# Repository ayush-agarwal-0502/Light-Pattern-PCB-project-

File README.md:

# Light-Pattern-PCB-Project-

Fascinating patterns of glowing LED lights made by me on proteus and eagle cad . ( Also called Diwali / Christmas lights)

Skills - Digital Electronics , PCB desgining 

Softwares involved - Proteus , Eagle CAD 

Digital electronics concepts involved - Jhonson counter with removed feedback , clock frequency divider , demux, astable multivibrator, monostable multivibrator using 555 timer 

Please see the video demostration of the lighting system , the file is uploaded in this repository .

Also see ADDITIONAL ideas file for other circuits for light patterns which I invented but haven't implemented yet .

# Proteus image 

# Eagle CAD schematic 

# Eagle CAD Board file 

# Gerber File View

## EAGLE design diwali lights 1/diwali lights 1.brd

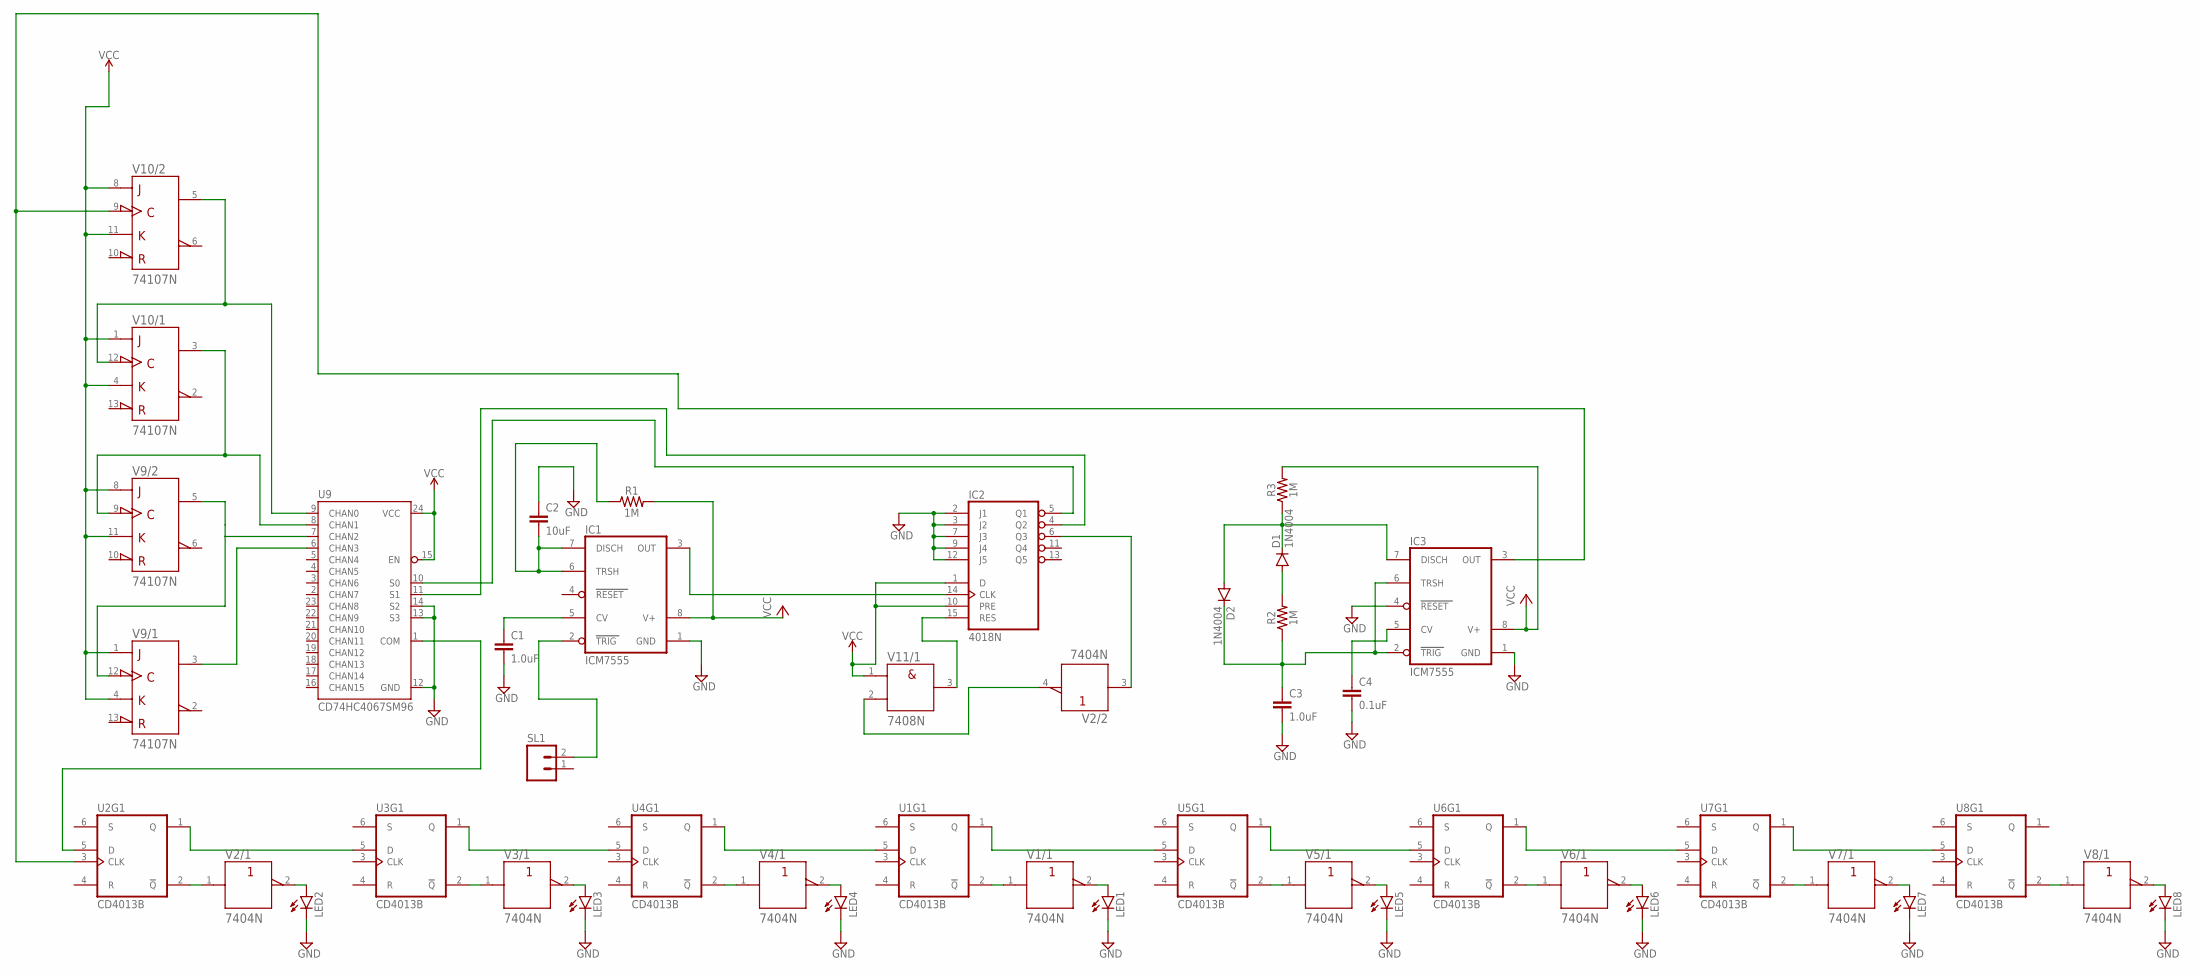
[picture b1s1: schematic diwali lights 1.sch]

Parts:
C1, C3: 1.0uF; 0402
C2: 10uF; 0805
C4: 0.1uF; 0402
D1, D2: 1N4004; DO41-10
IC1, IC3: ICM7555; DIL08
IC2: 4018N; DIL16
LED1, LED2, LED3, LED4, LED5, LED6, LED7, LED8: LED5MM
R1: 1M; 0402
R2, R3: 1M; AXIAL-0.3
SL1: M02; 02P
U1, U2, U3, U4, U5, U6, U7, U8: CD4013B; DIP14-KIT
U9: CD74HC4067SM96; SSOP24
V1, V2, V3, V4, V5, V6, V7, V8: 7404N; DIL14
V9, V10: 74107N; DIL14
V11: 7408N; DIL14

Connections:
+UB: V1.14 (+UB), V2.14 (+UB), V3.14 (+UB), V4.14 (+UB), V5.14 (+UB), V6.14 (+UB), V7.14 (+UB), V8.14 (+UB), V9.14 (+UB), V10.14 (+UB), V11.14 (+UB)
-UB: V1.7 (-UB), V2.7 (-UB), V3.7 (-UB), V4.7 (-UB), V5.7 (-UB), V6.7 (-UB), V7.7 (-UB), V8.7 (-UB), V9.7 (-UB), V10.7 (-UB), V11.7 (-UB)
GND: C1.2, C2.1, C3.2, C4.2, IC1.1 (GND), IC2.2 (J1), IC2.3 (J2), IC2.7 (J3), IC2.9 (J4), IC2.12 (J5), IC3.1 (GND), IC3.4 (RESET), LED1.K (C), LED2.K (C), LED3.K (C), LED4.K (C), LED5.K (C), LED6.K (C), LED7.K (C), LED8.K (C), U9.12 (GND), U9.13 (S3), U9.14 (S2)
unnamed: U1.2 (!Q), V1.1 (A)
unnamed: LED1.A, V1.2 (Y)
unnamed: U2.2 (!Q), V2.1 (A)
unnamed: LED2.A, V2.2 (Y)
unnamed: U3.2 (!Q), V3.1 (A)
unnamed: LED3.A, V3.2 (Y)
unnamed: U4.2 (!Q), V4.1 (A)
unnamed: LED4.A, V4.2 (Y)
unnamed: U5.2 (!Q), V5.1 (A)
unnamed: LED5.A, V5.2 (Y)
unnamed: U6.2 (!Q), V6.1 (A)
unnamed: LED6.A, V6.2 (Y)
unnamed: U7.2 (!Q), V7.1 (A)
unnamed: LED7.A, V7.2 (Y)
unnamed: U8.2 (!Q), V8.1 (A)
unnamed: LED8.A, V8.2 (Y)
unnamed: U2.1 (Q), U3.5 (D)
unnamed: U7.1 (Q), U8.5 (D)
unnamed: U3.1 (Q), U4.5 (D)
unnamed: U1.5 (D), U4.1 (Q)
unnamed: U1.1 (Q), U5.5 (D)
unnamed: U5.1 (Q), U6.5 (D)
unnamed: U6.1 (Q), U7.5 (D)
unnamed: U9.6 (CHAN3), V9.3 (Q)
unnamed: U2.5 (D), U9.1 (COM)
unnamed: U9.9 (CHAN0), V10.5 (Q), V10.12 (CLK)
unnamed: U9.8 (CHAN1), V9.9 (CLK), V10.3 (Q)
unnamed: U9.7 (CHAN2), V9.5 (Q), V9.12 (CLK)
unnamed: C3.1, D2.C, IC3.2 (TRIG), IC3.6 (TRSH), R2.P$1 (1)
unnamed: C2.2, IC1.6 (TRSH), IC1.7 (DISCH), R1.1
unnamed: C1.1, IC1.5 (CV)
unnamed: IC1.2 (TRIG), SL1.2
unnamed: IC2.6 (Q3), V2.3 (A)
unnamed: V2.4 (Y), V11.2 (B)
unnamed: IC1.3 (OUT), IC2.14 (CLK)
unnamed: IC2.15 (RES), V11.3 (Y)
unnamed: IC2.5 (Q1), U9.10 (S0)
unnamed: IC2.4 (Q2), U9.11 (S1)
unnamed: D1.A, R2.P$2 (2)
unnamed: D1.C, D2.A, IC3.7 (DISCH), R3.P$1 (1)
unnamed: C4.1, IC3.5 (CV)
unnamed: IC3.3 (OUT), U2.3 (CLK), V10.9 (CLK)
VCC: IC1.8 (V+), IC2.1 (D), IC2.10 (PRE), IC3.8 (V+), R1.2, R3.P$2 (2), U9.15 (EN), U9.24 (VCC), V9.1 (J), V9.4 (K), V9.8 (J), V9.11 (K), V10.1 (J), V10.4 (K), V10.8 (J), V10.11 (K), V11.1 (A)
VDD: IC2.16 (VDD)
VSS: IC2.8 (VSS)

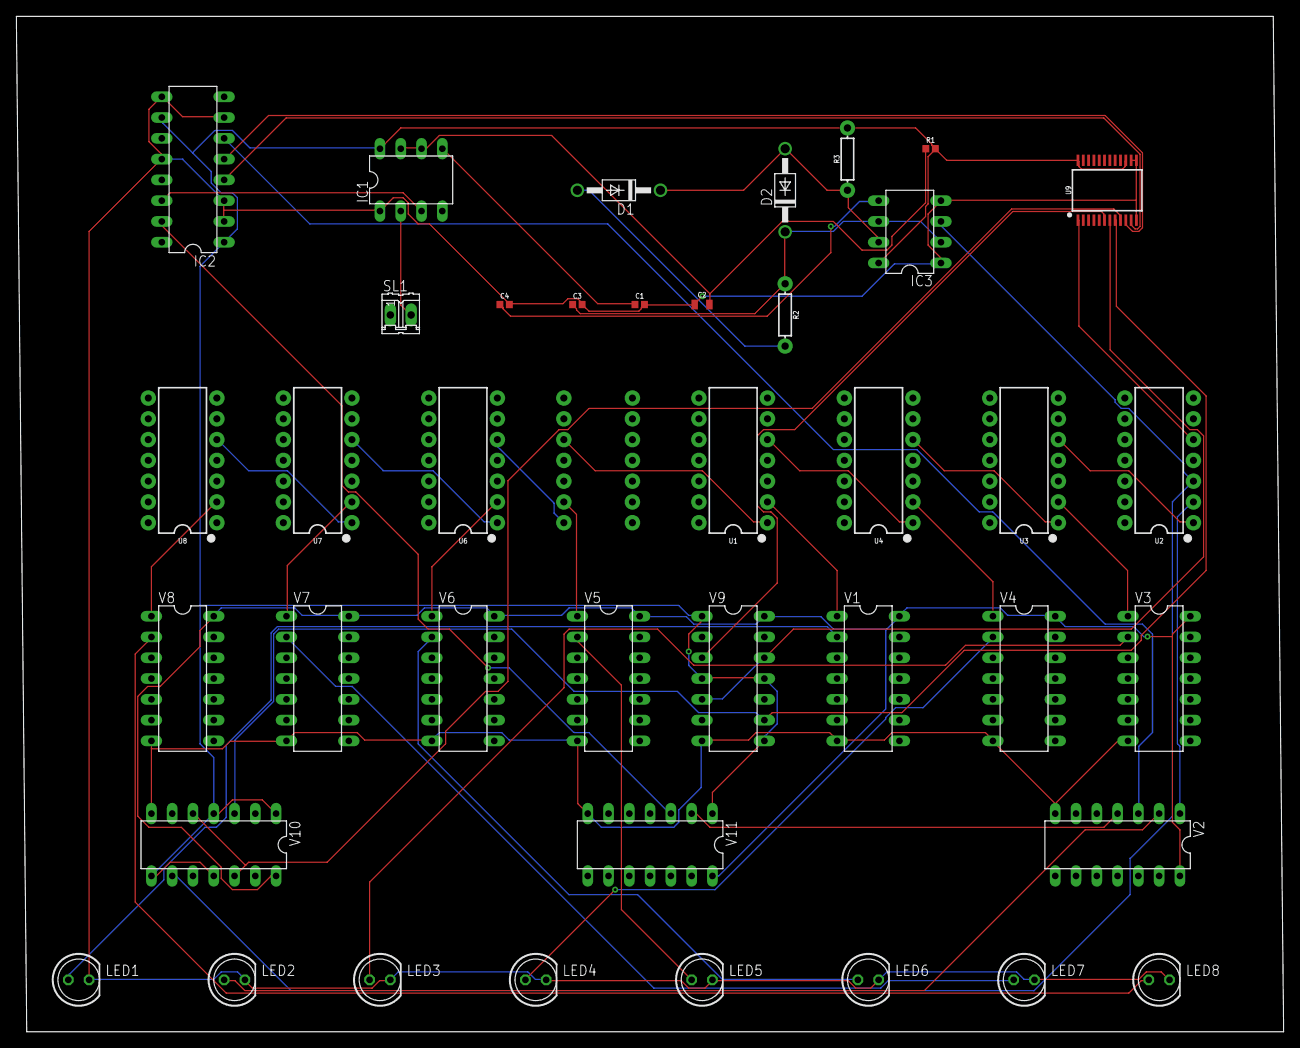
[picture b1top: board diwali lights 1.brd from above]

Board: 2 copper layers, 154.9 x 124.1 mm, 41 parts (1 on the bottom side), 46 nets.

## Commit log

2021-12-01 commiting the project files including the gerber , images , video demonstration , manufacturing files etc

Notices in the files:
parts and their libraries:
SparkFun-Capacitors: Licensing: Creative Commons ShareAlike 4.0 International - https://creativecommons.org/licenses/by-sa/4.0
